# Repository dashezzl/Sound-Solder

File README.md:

# Sound & Solder
A self replicating synthesiser

The installation inscribes itself in the tradition of the Synthesizer Do It Yourself (SDIY) scene and is based on its knowledge. The aim of the installation is to give insight into the world of homemade electronic instruments. The community ́s mode of practice relies on constant re-creation and enhancement, therefore our installation is able to recreate and expand itself by etching new circuit boards. The work provides detailed instructions and all the necessary plans to rebuild it. What makes this installation particular is that it emphasizes iteration as a key element in the SDIY community. Not only did we based it on replicating existing open source designs, but the elements of the installation are multiplying themselves by re-creating and expanding their working parts by etching new circuit boards.

# sdiy # synthforthemasses # analogisnonbinary #

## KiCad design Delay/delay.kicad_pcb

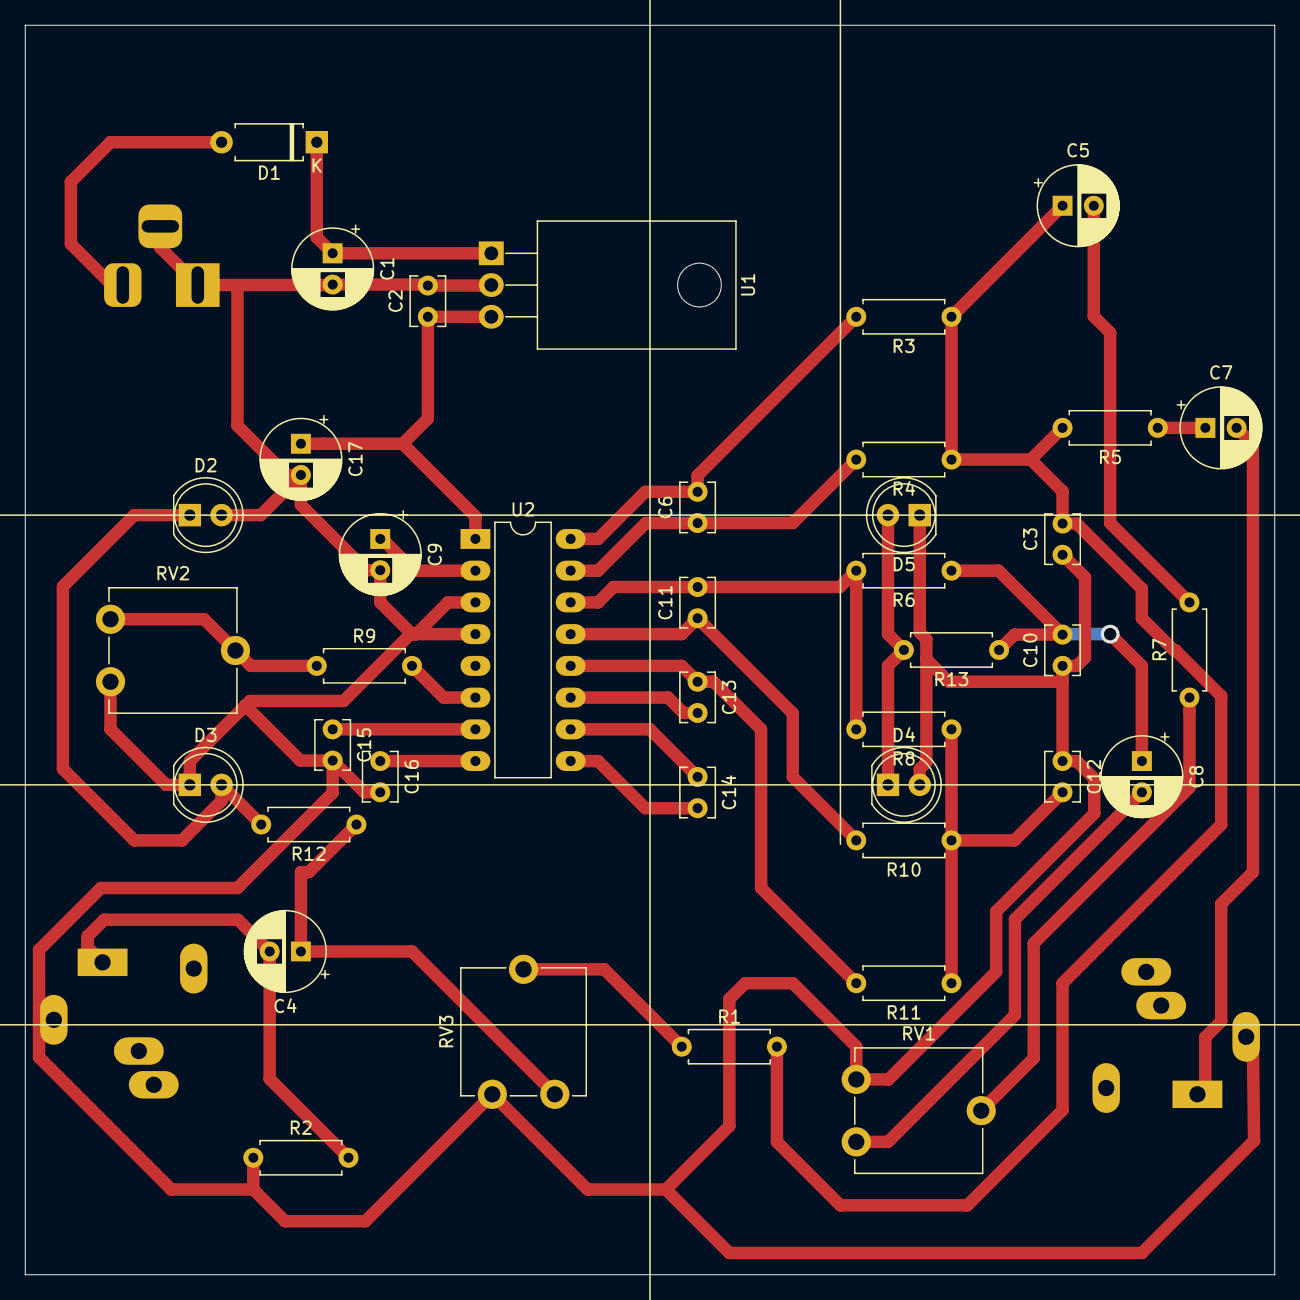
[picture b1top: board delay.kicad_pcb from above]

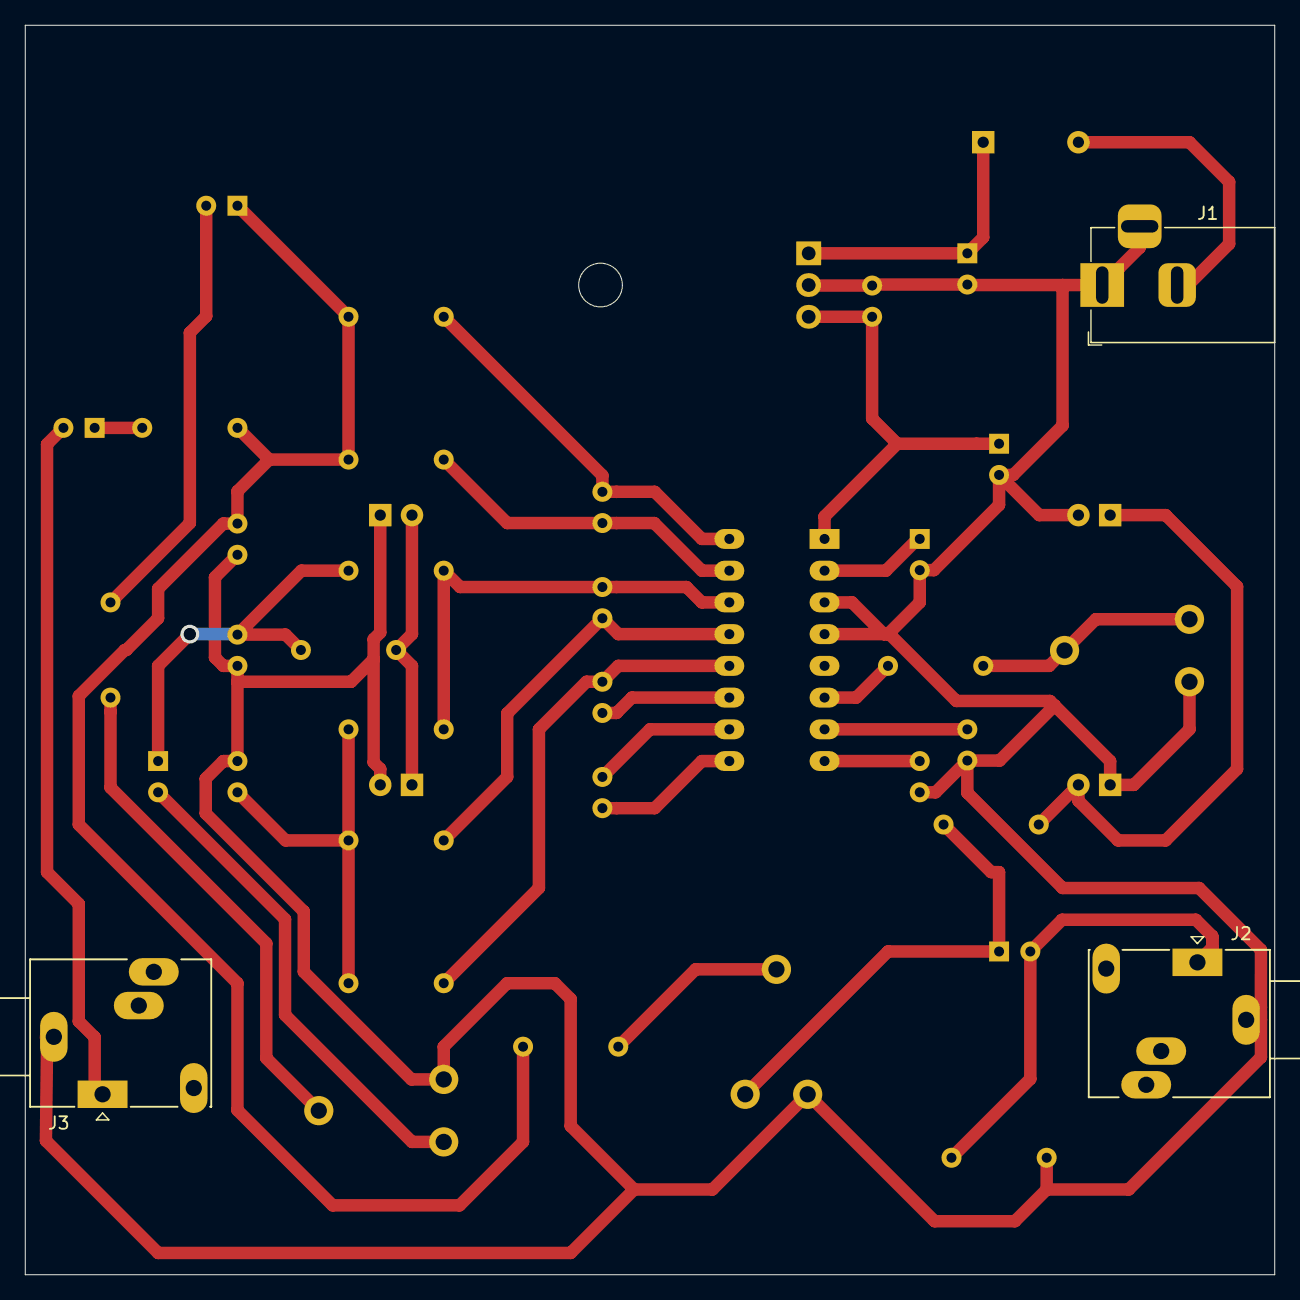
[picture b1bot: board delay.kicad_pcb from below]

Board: 2 copper layers, 100.0 x 100.0 mm, 43 parts (3 on the bottom side), 30 nets.

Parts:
C1, C8, C17: 10u; CP_Radial_D6.3mm_P2.50mm
C2, C15, C16: 100n; C_Disc_D3.8mm_W2.6mm_P2.50mm
C3: 3,9n; C_Disc_D3.8mm_W2.6mm_P2.50mm
C4, C5, C7: 4,7u; CP_Radial_D6.3mm_P2.50mm
C6, C11: 560p; C_Disc_D3.8mm_W2.6mm_P2.50mm
C9: 47u; CP_Radial_D6.3mm_P2.50mm
C10: 10n; C_Disc_D3.8mm_W2.6mm_P2.50mm
C12: 3,3n; C_Disc_D3.8mm_W2.6mm_P2.50mm
C13, C14: 82n; C_Disc_D3.8mm_W2.6mm_P2.50mm
D1: D; D_A-405_P7.62mm_Horizontal
D2, D3: In; LED_D5.0mm
D4, D5: Delay; LED_D5.0mm
J1: Barrel_Jack_Switch; BarrelJack_Horizontal
J2: In; Jack_3.5mm_Ledino_KB3SPRS_Horizontal
J3: Out; Jack_3.5mm_Ledino_KB3SPRS_Horizontal
R1, R2, R8: 15k; R_Axial_DIN0207_L6.3mm_D2.5mm_P7.62mm_Horizontal
R3, R4, R7, R10, R11, R12, R13: 10k; R_Axial_DIN0207_L6.3mm_D2.5mm_P7.62mm_Horizontal
R5: 4,7k; R_Axial_DIN0207_L6.3mm_D2.5mm_P7.62mm_Horizontal
R6: 5,6k; R_Axial_DIN0207_L6.3mm_D2.5mm_P7.62mm_Horizontal
R9: 2,2k; R_Axial_DIN0207_L6.3mm_D2.5mm_P7.62mm_Horizontal
RV1: 50k; Potentiometer_ACP_CA9-V10_Vertical
RV2, RV3: 100k; Potentiometer_ACP_CA9-V10_Vertical
U1: L7805; TO-220-3_Horizontal_TabDown
U2: PT2399; DIP-16_W7.62mm_LongPads

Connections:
+5V: C2.1, C17.1, U1.3, U2.1
+12V: D1.2, J1.2
GND: C1.2, C2.2, C3.1, C9.2, C10.1, C12.1, C15.2, C16.2, C17.2, D2.2, D3.1, D4.2, D5.1, J1.1, J1.3, J2.S, J3.S, R2.1, RV1.3, RV2.1, RV3.3, U1.2, U2.3, U2.4
unnamed: C1.1, D1.1, U1.1
unnamed: C3.2, C5.1, R1.2, R3.1, R4.1, R5.2
unnamed: C4.1, R12.1, RV3.1
unnamed: C4.2, J2.T, R2.2
unnamed: C5.2, R7.2
unnamed: C6.1, R4.2, U2.15
unnamed: C6.2, R3.2, U2.16
unnamed: C7.1, R5.1
unnamed: C7.2, J3.T
unnamed: C8.2, RV1.1
unnamed: C9.1, U2.2
unnamed: C8.1, C10.2, R6.1, R13.1
unnamed: C11.1, R10.2, U2.13
unnamed: C11.2, R6.2, R8.2, U2.14
unnamed: C12.2, R8.1, R10.1, R11.1
unnamed: C13.1, R11.2, U2.12
unnamed: C13.2, U2.11
unnamed: C14.1, U2.10
unnamed: C14.2, U2.9
unnamed: C15.1, U2.7
unnamed: C16.1, U2.8
unnamed: D2.1, D3.2, R12.2
unnamed: D4.1, D5.2, R13.2
unnamed: R1.1, RV3.2
unnamed: R7.1, RV1.2
unnamed: R9.1, RV2.2, RV2.3
unnamed: R9.2, U2.6

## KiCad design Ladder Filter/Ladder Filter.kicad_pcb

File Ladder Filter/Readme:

Ladder Filter
Based on Moog Ladder Filter
/revisions of it from Yu Synth, Kassutronics and Om Synth .

http://yusynth.net/Modular/index_en.html
https://kassu2000.blogspot.com/2018/07/transistor-ladder-filter.html
https://omsonic.co.uk/product/omsonic-transistor-ladder-filter-full-kit-2/

Dont forget to match the transistors and capacitors in the ladder!
Link for transistor testing:
https://kassu2000.blogspot.com/2015/10/transistor-matching.html

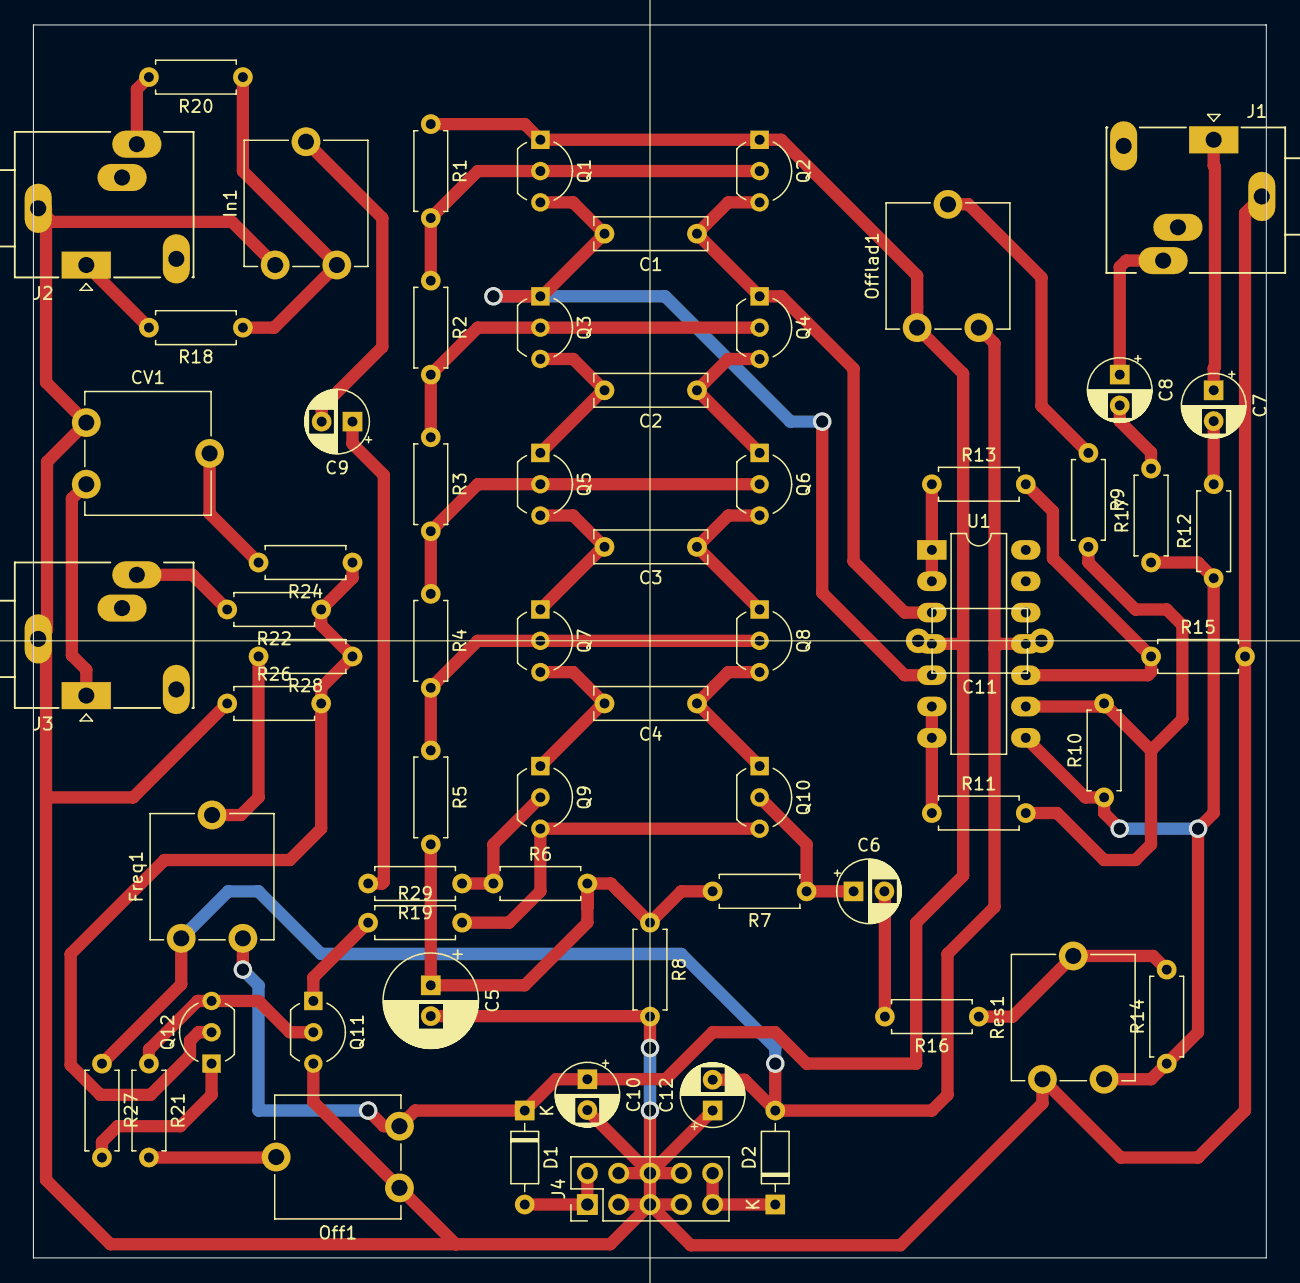
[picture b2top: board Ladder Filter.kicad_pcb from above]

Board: 2 copper layers, 100.0 x 100.0 mm, 64 parts (0 on the bottom side), 47 nets.

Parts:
C1, C2, C3, C4: 47n; C_Rect_L9.0mm_W2.5mm_P7.50mm_MKT
C5: 220u; CP_Radial_D7.5mm_P2.50mm
C6, C7, C8, C9, C10, C12: 10u; CP_Radial_D5.0mm_P2.50mm
C11: 100n; C_Disc_D7.5mm_W5.0mm_P10.00mm
CV1: 100k; Potentiometer_ACP_CA9-V10_Vertical
D1, D2: D; D_DO-35_SOD27_P7.62mm_Horizontal
Freq1: 100k; Potentiometer_ACP_CA9-V10_Vertical
In1: 10k; Potentiometer_ACP_CA9-V10_Vertical
J1: Out; Jack_3.5mm_Ledino_KB3SPRS_Horizontal
J2: In; Jack_3.5mm_Ledino_KB3SPRS_Horizontal
J3: Cv; Jack_3.5mm_Ledino_KB3SPRS_Horizontal
J4: EURO_PWR_2x5; PinHeader_2x05_P2.54mm_Vertical
Off1: 100k; Potentiometer_ACP_CA9-V10_Vertical
Offlad1: 100k; Potentiometer_ACP_CA9-V10_Vertical
Q1, Q2, Q3, Q4, Q5, Q6, Q7, Q8, Q9, Q10, Q11: BC547; TO-92_Inline_Wide
Q12: BC557; TO-92_Inline_Wide
R1, R2, R3, R4, R5, R8: 220; R_Axial_DIN0207_L6.3mm_D2.5mm_P7.62mm_Horizontal
R6, R7: 470; R_Axial_DIN0207_L6.3mm_D2.5mm_P7.62mm_Horizontal
R9: 1m; R_Axial_DIN0207_L6.3mm_D2.5mm_P7.62mm_Horizontal
R10, R15, R21, R22, R24, R28: 100k; R_Axial_DIN0207_L6.3mm_D2.5mm_P7.62mm_Horizontal
R11, R13: 1,5k; R_Axial_DIN0207_L6.3mm_D2.5mm_P7.62mm_Horizontal
R12, R17, R18, R20, R29: 1k; R_Axial_DIN0207_L6.3mm_D2.5mm_P7.62mm_Horizontal
R14: 4,7k; R_Axial_DIN0207_L6.3mm_D2.5mm_P7.62mm_Horizontal
R16: 6,8k; R_Axial_DIN0207_L6.3mm_D2.5mm_P7.62mm_Horizontal
R19: 9k; R_Axial_DIN0207_L6.3mm_D2.5mm_P7.62mm_Horizontal
R26, R27: 1,2k; R_Axial_DIN0207_L6.3mm_D2.5mm_P7.62mm_Horizontal
Res1: 10k; Potentiometer_ACP_CA9-V10_Vertical
U1: TL074; DIP-14_W7.62mm_LongPads

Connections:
+12V: C10.1, C11.2, D1.1, Freq1.1, Off1.1, Offlad1.3, Q1.1, Q2.1, R1.1, U1.4
-12V: C11.1, C12.2, D2.2, Freq1.3, Offlad1.1, R27.1, U1.11
CV: Q11.1, R29.1
GND: C5.2, C10.2, C12.1, CV1.3, In1.3, J1.S, J2.S, J3.S, J4.3, J4.4, J4.5, J4.6, J4.7, J4.8, Off1.3, Q11.3, R8.2, R15.2, R26.1, Res1.3
IN: Q9.2, R6.1, R19.1
unnamed: C2.1, Q4.3, Q6.1
unnamed: C2.2, Q3.3, Q5.1
unnamed: C3.1, Q6.3, Q8.1
unnamed: C3.2, Q5.3, Q7.1
unnamed: C4.1, Q8.3, Q10.1
unnamed: C4.2, Q7.3, Q9.1
unnamed: C5.1, R5.2, R6.2, R7.2, R8.1
unnamed: C6.2, R16.2
unnamed: C7.1, J1.T
unnamed: C7.2, R12.2
unnamed: C8.1, J1.R
unnamed: C8.2, R17.2
unnamed: C9.1, R19.2
unnamed: C9.2, In1.2
unnamed: CV1.1, J3.T
unnamed: CV1.2, R24.2
unnamed: D1.2, J4.1, J4.2
unnamed: D2.1, J4.9, J4.10
unnamed: Freq1.2, R28.2
unnamed: In1.1, R18.1, R20.1
unnamed: J2.R, R20.2
unnamed: J2.T, R18.2
unnamed: J3.R, R22.2
unnamed: Off1.2, R21.2
unnamed: Offlad1.2, R9.1
unnamed: Q1.2, Q2.2, R1.2, R2.1
unnamed: Q3.2, Q4.2, R2.2, R3.1
unnamed: Q5.2, Q6.2, R3.2, R4.1
unnamed: Q7.2, Q8.2, R4.2, R5.1
unnamed: Q9.3, Q10.3, R29.2
unnamed: Q11.2, Q12.3, R21.1
unnamed: Q12.1, R27.2
unnamed: Q12.2, R22.1, R24.1, R26.2, R28.1
unnamed: R10.1, R12.1, R14.1, R17.1, Res1.1, U1.8
unnamed: R9.2, R10.2, R11.2, U1.9
unnamed: R11.1, U1.6, U1.7
unnamed: R13.1, U1.1, U1.2
unnamed: R13.2, R15.1, U1.10
unnamed: R14.2, R16.1, Res1.2
Out1: C1.2, Q1.3, Q3.1, U1.5
Out2: C1.1, Q2.3, Q4.1, U1.3
RES: C6.1, Q10.2, R7.1

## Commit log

2021-01-14 Create Info
2021-01-14 Rename Readme to Info
2021-01-14 Rename Info to Readme
